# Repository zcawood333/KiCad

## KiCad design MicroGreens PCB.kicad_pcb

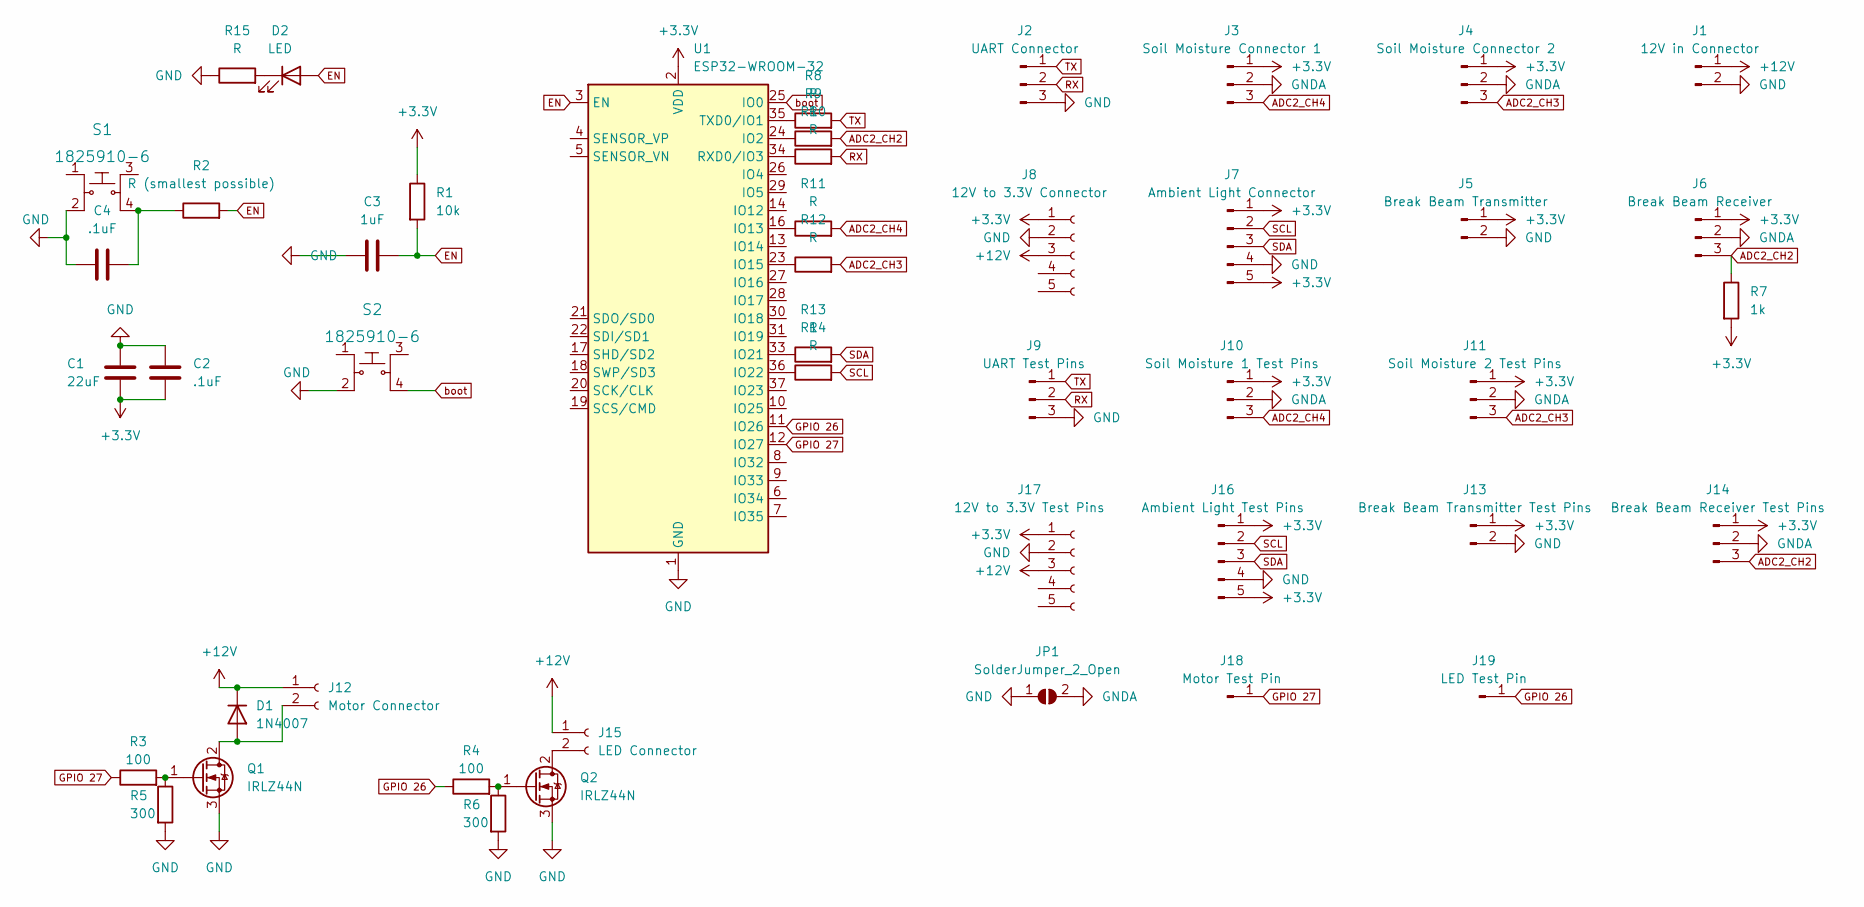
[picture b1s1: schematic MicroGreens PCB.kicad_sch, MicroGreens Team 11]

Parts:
C1: 22uF; C_Disc_D5.0mm_W2.5mm_P5.00mm
C2, C4: .1uF; C_Disc_D5.0mm_W2.5mm_P5.00mm
C3: 1uF; C_Disc_D5.0mm_W2.5mm_P5.00mm
D1: 1N4007; D_DO-41_SOD81_P10.16mm_Horizontal
D2: LED; LED_D3.0mm
J1: 12V in Connector; TE_640445-2
J2: UART Connector; PinHeader_1x03_P2.54mm_Vertical
J3: Soil Moisture Connector 1; TE_640388-3
J4: Soil Moisture Connector 2; TE_640388-3
J5: Break Beam Transmitter; TE_640445-2
J6: Break Beam Receiver; TE_640388-3
J7: Ambient Light Connector; TE_640445-5
J8: 12V to 3.3V Connector; PinHeader_1x05_P2.54mm_Vertical
J9: UART Test Pins; PinHeader_1x03_P2.54mm_Vertical
J10: Soil Moisture 1 Test Pins; PinHeader_1x03_P2.54mm_Vertical
J11: Soil Moisture 2 Test Pins; PinHeader_1x03_P2.54mm_Vertical
J12: Motor Connector; TE_640445-2
J13: Break Beam Transmitter Test Pins; PinHeader_1x02_P2.54mm_Vertical
J14: Break Beam Receiver Test Pins; PinHeader_1x03_P2.54mm_Vertical
J15: LED Connector; TE_640445-2
J16: Ambient Light Test Pins; PinHeader_1x05_P2.54mm_Vertical
J17: 12V to 3.3V Test Pins; PinHeader_1x05_P2.54mm_Vertical
J18: Motor Test Pin; PinHeader_1x01_P2.54mm_Vertical
J19: LED Test Pin; PinHeader_1x01_P2.54mm_Vertical
JP1: SolderJumper_2_Open; SolderJumper-2_P1.3mm_Open_RoundedPad1.0x1.5mm
Q1, Q2: IRLZ44N; TO-220-3_Vertical
R1: 10k; R_Axial_DIN0207_L6.3mm_D2.5mm_P7.62mm_Horizontal
R2: R (smallest possible); R_Axial_DIN0207_L6.3mm_D2.5mm_P7.62mm_Horizontal
R3, R4: 100; R_Axial_DIN0207_L6.3mm_D2.5mm_P7.62mm_Horizontal
R5, R6: 300; R_Axial_DIN0207_L6.3mm_D2.5mm_P7.62mm_Horizontal
R7: 1k; R_Axial_DIN0207_L6.3mm_D2.5mm_P7.62mm_Horizontal
R8, R9, R10, R11, R12, R13, R14, R15: R; R_Axial_DIN0207_L6.3mm_D2.5mm_P7.62mm_Horizontal
S1, S2: 1825910-6; Switch_Tactile_THT_6x6mm; MPN 1825910-6; Digi-Key_PN 450-1650-ND
U1: ESP32-WROOM-32

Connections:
+3V3: C1.2, C2.2, J3.1, J4.1, J5.1, J6.1, J7.1, J7.5, J8.1, J10.1, J11.1, J13.1, J14.1, J16.1, J16.5, J17.1, R1.1, R7.2, U1.2 (VDD)
+12V: D1.1 (K), J1.1, J8.3, J12.1, J15.1, J17.3
ADC2_CH2: J6.3, J14.3, R7.1, R9.2
ADC2_CH3: J4.3, J11.3, R12.2
ADC2_CH4: J3.3, J10.3, R11.2
EN: C3.2, D2.2 (A), R1.2, R2.2, U1.3 (EN)
GND: C1.1, C2.1, C3.1, C4.1, J1.2, J2.3, J5.2, J7.4, J8.2, J9.3, J13.2, J16.4, J17.2, JP1.1 (A), Q1.3 (S), Q2.3 (S), R5.2, R6.2, R15.1, S1.2, S2.2, U1.1 (GND), U1.15 (GND), U1.38 (GND), U1.39 (GND)
GNDA: J3.2, J4.2, J6.2, J10.2, J11.2, J14.2, JP1.2 (B)
GPIO 26: J19.1, R4.1, U1.11 (IO26)
GPIO 27: J18.1, R3.1, U1.12 (IO27)
unnamed: C4.2, R2.1, S1.4
unnamed: D1.2 (A), J12.2, Q1.2 (D)
unnamed: D2.1 (K), R15.2
unnamed: J15.2, Q2.2 (D)
unnamed: Q1.1 (G), R3.2, R5.1
unnamed: Q2.1 (G), R4.2, R6.1
unnamed: R11.1, U1.16 (IO13)
unnamed: R12.1, U1.23 (IO15)
unnamed: R9.1, U1.24 (IO2)
unnamed: R13.1, U1.33 (IO21)
unnamed: R10.1, U1.34 (RXD0/IO3)
unnamed: R8.1, U1.35 (TXD0/IO1)
unnamed: R14.1, U1.36 (IO22)
RX: J2.2, J9.2, R10.2
SCL: J7.2, J16.2, R14.2
SDA: J7.3, J16.3, R13.2
TX: J2.1, J9.1, R8.2
boot: S2.4, U1.25 (IO0)

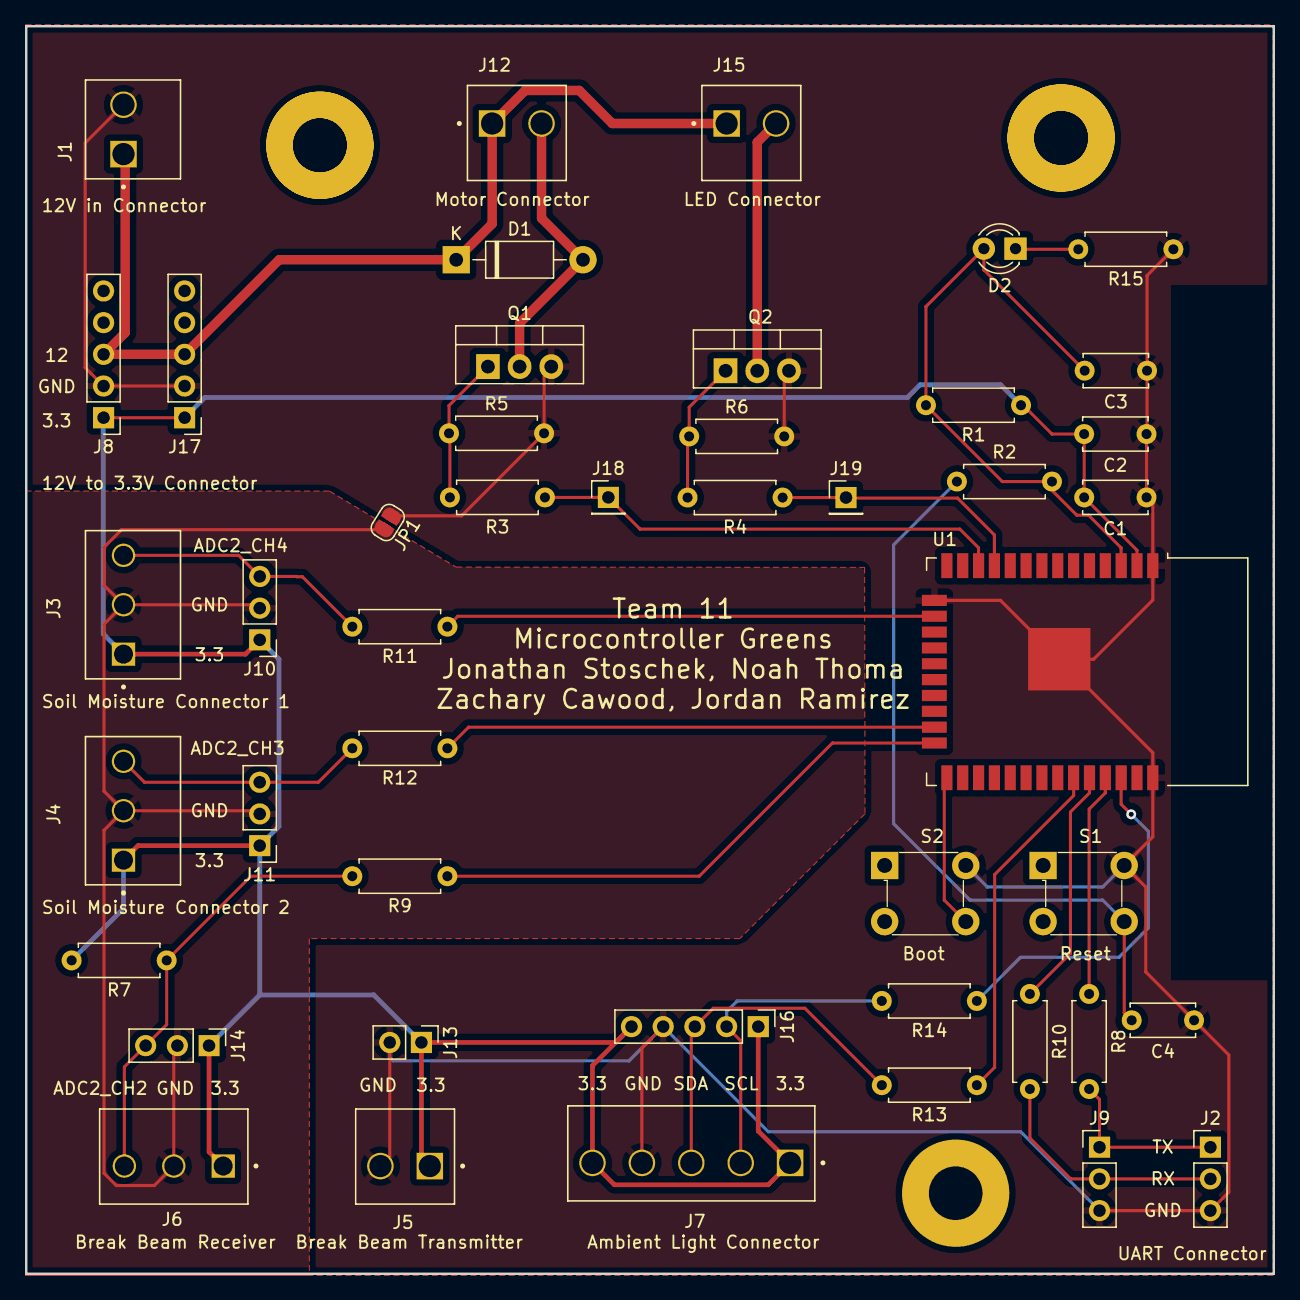
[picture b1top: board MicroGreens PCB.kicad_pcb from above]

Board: 2 copper layers, 100.0 x 100.0 mm, 48 parts (0 on the bottom side), 28 nets.

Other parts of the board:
S1#2, S1#3: MountingHole_4.3mm_M4_Pad
